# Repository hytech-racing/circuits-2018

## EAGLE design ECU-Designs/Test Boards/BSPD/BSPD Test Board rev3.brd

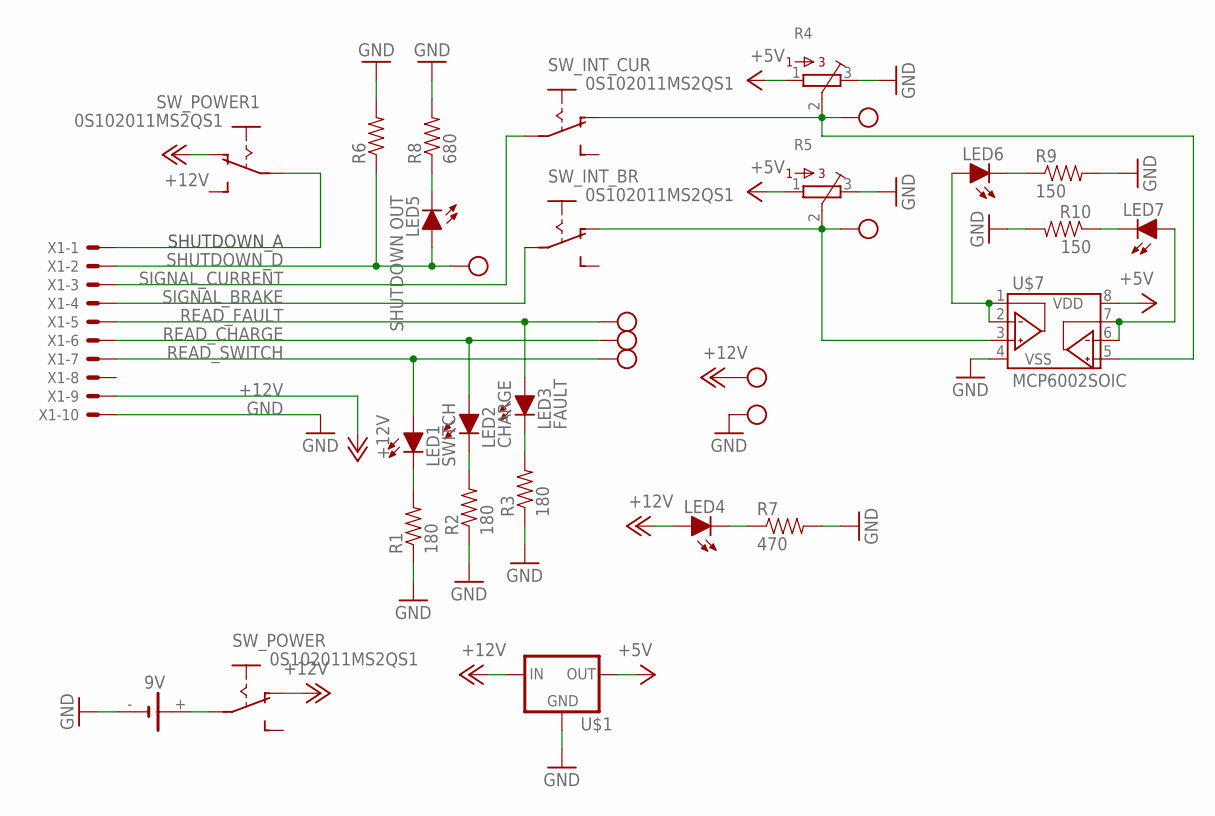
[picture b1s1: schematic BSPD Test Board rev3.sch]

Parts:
9V: 1291-79
LED1: SWITCH; LED-5MM
LED2: CHARGE; LED-5MM
LED3: FAULT; LED-5MM
LED4, LED6, LED7: LED-0805; LED-805
LED5: SHUTDOWN OUT; LED-5MM
R1, R2, R3: 180; 0805
R4, R5: TRIMPOT_3296C; TRIMPOT_3296
R6: RESISTORPTH-1/2W; AXIAL-0.5
R7: 470; 0805
R8: 680; 0805
R9, R10: 150; 0805
SW_INT_BR: 0S102011MS2QS1
SW_INT_CUR: 0S102011MS2QS1
SW_POWER, SW_POWER1: 0S102011MS2QS1
U$1: 5VREG_LM340-NLM340MPX-5.0/NOPB; SOT223
U$2, U$3, U$4, U$5, U$6, U$8, U$9, U$10: TEST_POINT
U$7: MCP6002SOIC; SOIC-08
X1: CONNECTOR-10; MINIFIT_5566-10

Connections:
+5V: R4.1, R5.1, U$1.3 (OUT), U$7.8 (VDD)
+12V: LED4.A, SW_POWER.P$1 (O), SW_POWER1.P$1 (O), U$1.1 (IN), U$5.P$1, X1.9
GND: 9V.-, R1.1, R2.1, R3.1, R4.3, R5.3, R6.P$2 (2), R7.2, R8.2, R9.2, R10.2, U$1.2 (GND), U$1.4 (GND), U$6.P$1, U$7.4 (VSS), X1.10
unnamed: LED1.K (C), R1.2
unnamed: LED2.K (C), R2.2
unnamed: LED3.K (C), R3.2
unnamed: R4.2, SW_INT_CUR.P$1 (O), U$2.P$1, U$7.5 (VINB+)
unnamed: R5.2, SW_INT_BR.P$1 (O), U$3.P$1, U$7.3 (VINA+)
unnamed: 9V.+, SW_POWER.P$2
unnamed: LED4.C, R7.1
unnamed: LED6.A, U$7.1 (VOUTA), U$7.2 (VINA-)
unnamed: LED7.A, U$7.6 (VINB-), U$7.7 (VOUTB)
unnamed: LED6.C, R9.1
unnamed: LED5.K (C), R8.1
unnamed: LED7.C, R10.1
unnamed: SW_POWER1.P$2, X1.1
READ_CHARGE: LED2.A, U$9.P$1, X1.6
READ_FAULT: LED3.A, U$8.P$1, X1.5
READ_SWITCH: LED1.A, U$10.P$1, X1.7
SHUTDOWN_D: LED5.A, R6.P$1 (1), U$4.P$1, X1.2
SIGNAL_BRAKE: SW_INT_BR.P$2, X1.4
SIGNAL_CURRENT: SW_INT_CUR.P$2, X1.3

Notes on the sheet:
SHUTDOWN_A

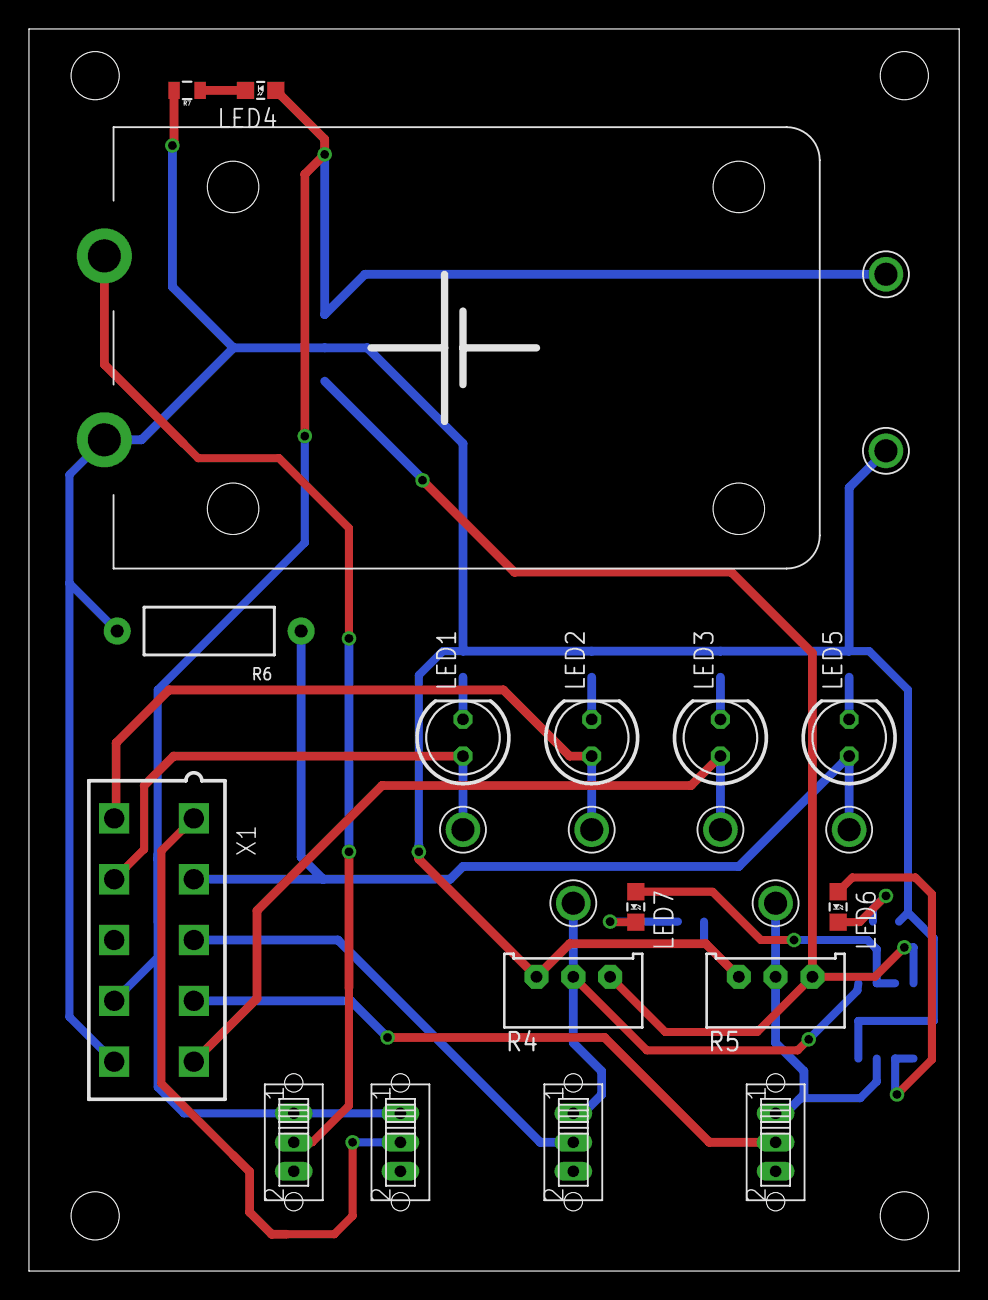
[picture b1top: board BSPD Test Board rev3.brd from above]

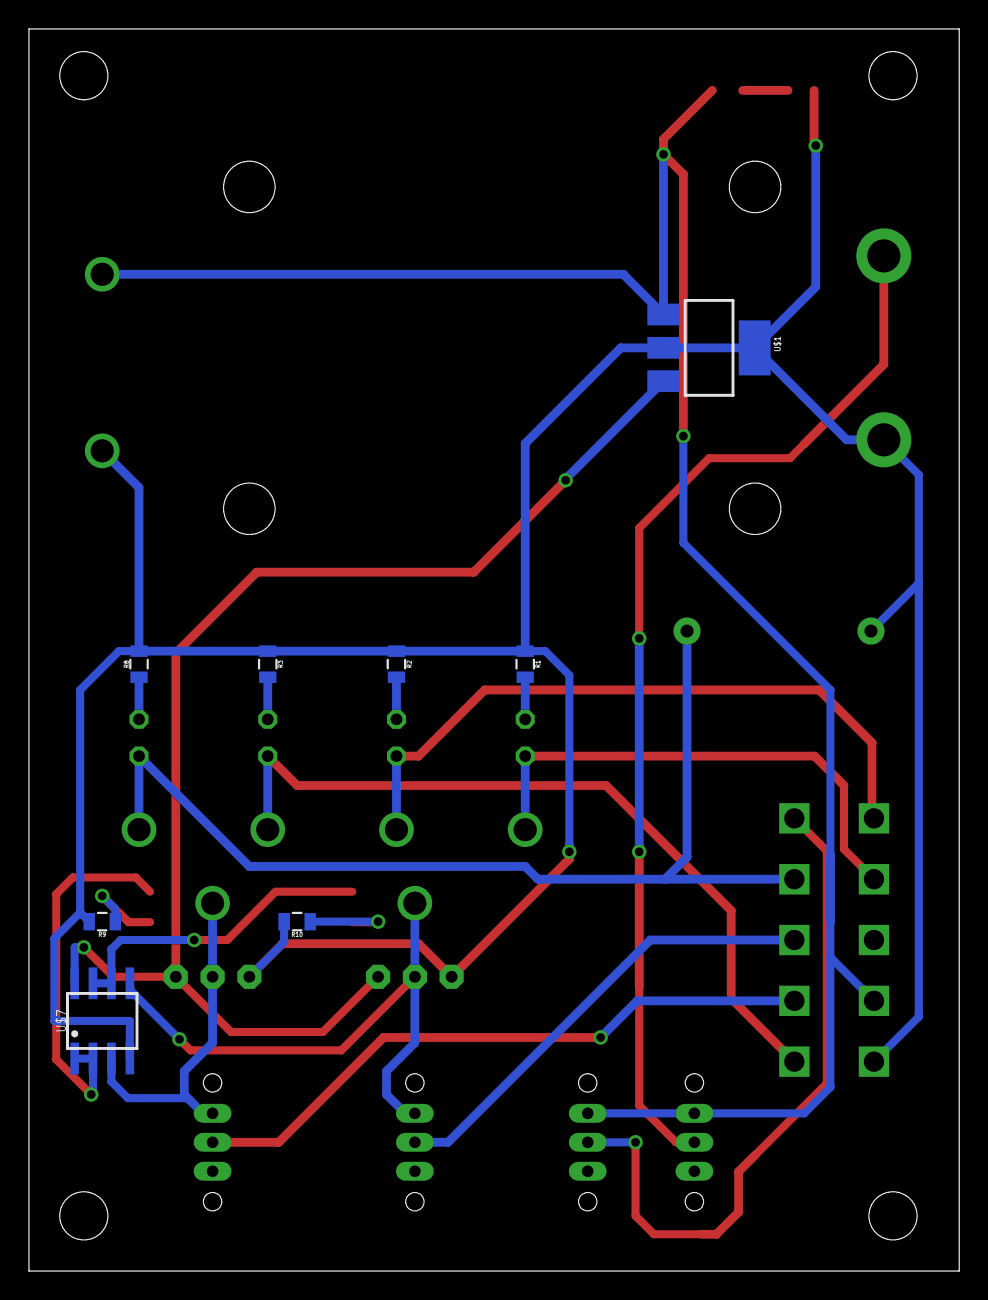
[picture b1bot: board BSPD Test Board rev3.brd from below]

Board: 2 copper layers, 64.2 x 85.8 mm, 33 parts (8 on the bottom side), 22 nets.

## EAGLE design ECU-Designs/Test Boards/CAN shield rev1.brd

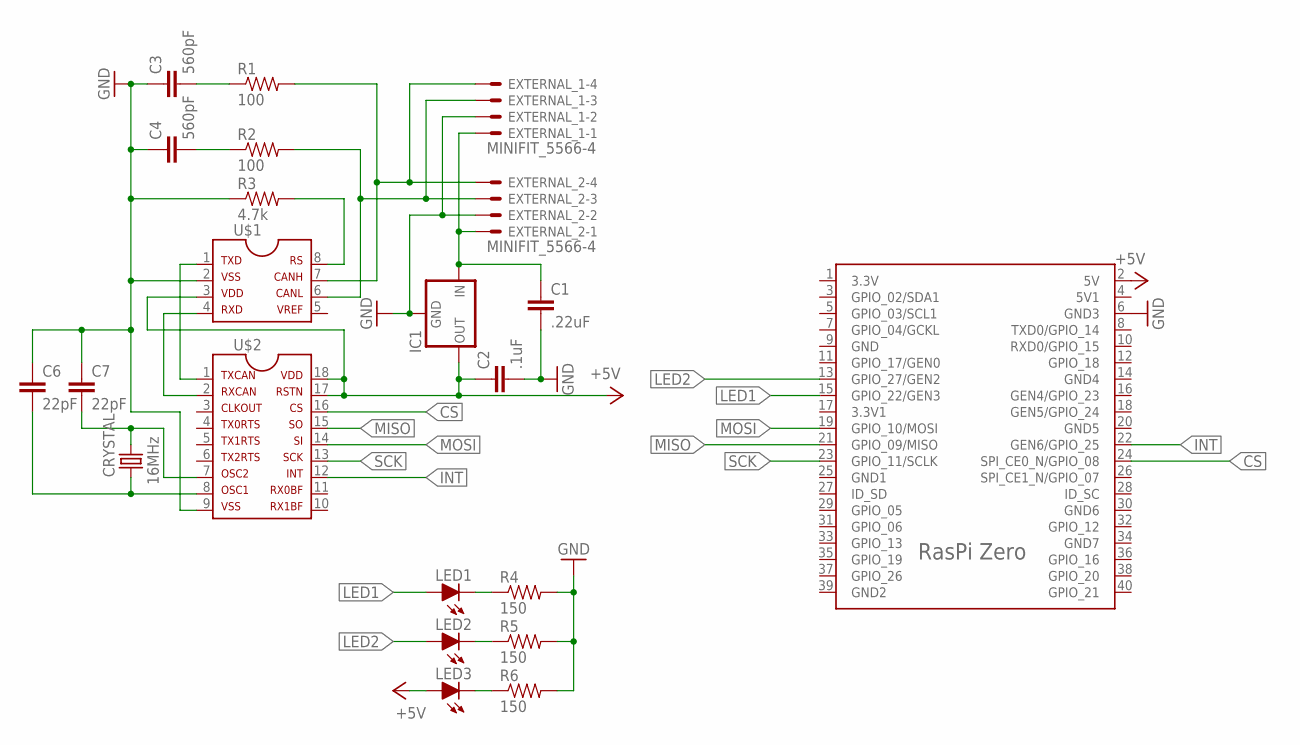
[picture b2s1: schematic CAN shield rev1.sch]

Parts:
C1: .22uF; 0805
C2: .1uF; 0805
C3, C4: 560pF; 0805
C6, C7: 22pF; 0805
CRYSTAL: 16MHz; HC49UP
EXTERNAL_1, EXTERNAL_2: MINIFIT_5566-4
IC1: 5VREG_L7805_HOR; TO-220-H
LED1, LED2, LED3: LED-0805; LED-805
R1, R2: 100; 0805
R3: 4.7k; 0805
R4, R5, R6: 150; 0805
U$1: MCP2551; SOIC-08
U$2: MCP2515SMD; SOIC-18W
U$3: RASPBERRY_PI_ZERO-V1.2

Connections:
+5V: C2.1, IC1.3 (OUT), LED3.A, U$1.3, U$2.17, U$2.18, U$3.2 (5V)
CAN-H: EXTERNAL_1.4, EXTERNAL_2.4, R1.2, U$1.7
CAN-L: EXTERNAL_1.3, EXTERNAL_2.3, R2.2, U$1.6
CS: U$2.16, U$3.24 (SPI_CE0_N/GPIO_08)
GND: C1.2, C2.2, C3.1, C4.1, C6.1, C7.1, EXTERNAL_1.2, EXTERNAL_2.2, IC1.2 (GND), R3.1, R4.2, R5.2, R6.2, U$1.2, U$2.9, U$3.6 (GND3)
INT: U$2.12, U$3.22 (GEN6/GPIO_25)
LED1: LED1.A, U$3.15 (GPIO_22/GEN3)
LED2: LED2.A, U$3.13 (GPIO_27/GEN2)
MISO: U$2.15, U$3.21 (GPIO_09/MISO)
MOSI: U$2.14, U$3.19 (GPIO_10/MOSI)
unnamed: LED1.C, R4.1
unnamed: LED2.C, R5.1
unnamed: C1.1, EXTERNAL_1.1, EXTERNAL_2.1, IC1.1 (IN)
unnamed: LED3.C, R6.1
unnamed: C6.2, CRYSTAL.2, U$2.8
unnamed: U$1.1, U$2.1
unnamed: U$1.4, U$2.2
unnamed: C3.2, R1.1
unnamed: C7.2, CRYSTAL.1, U$2.7
unnamed: R3.2, U$1.8
unnamed: C4.2, R2.1
SCK: U$2.13, U$3.23 (GPIO_11/SCLK)

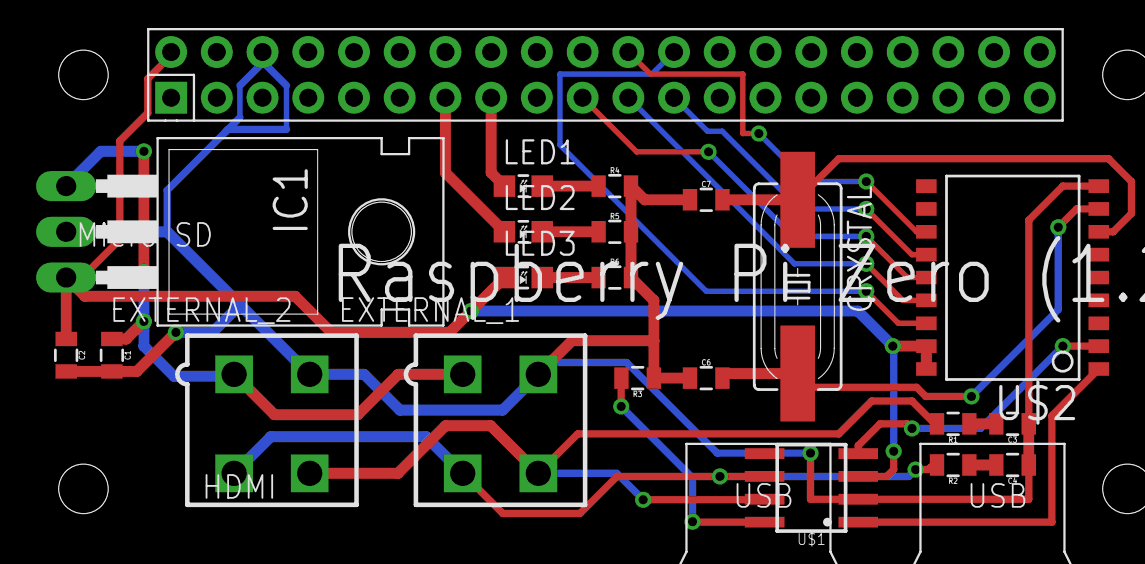
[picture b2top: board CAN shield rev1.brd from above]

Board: 2 copper layers, 22 parts (0 on the bottom side), 22 nets.

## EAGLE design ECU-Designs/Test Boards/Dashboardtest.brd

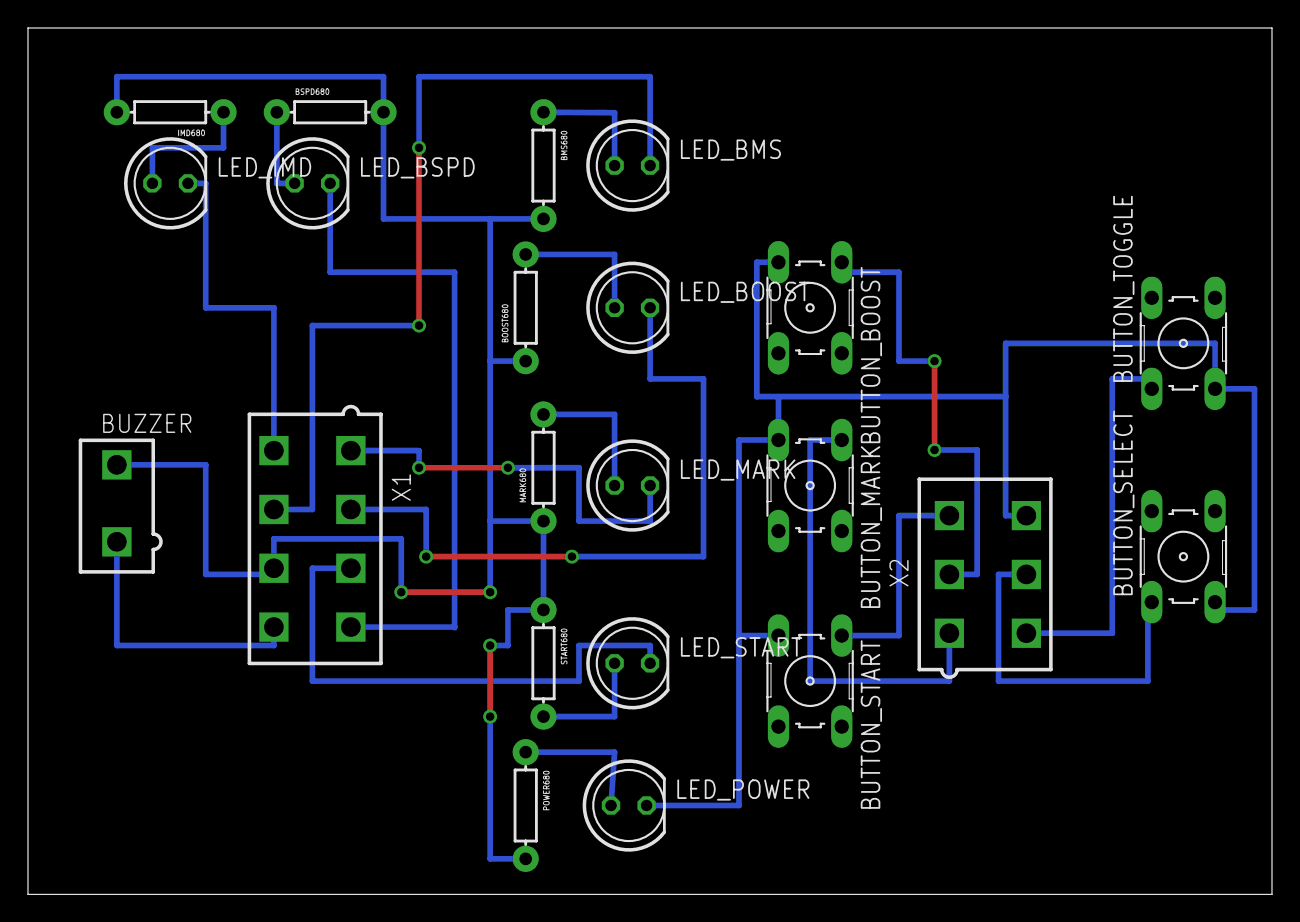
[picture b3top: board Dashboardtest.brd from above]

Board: 2 copper layers, 88.9 x 61.9 mm, 22 parts (0 on the bottom side), 21 nets.

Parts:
BMS680: AXIAL-0.3EZ
BOOST680: AXIAL-0.3EZ
BSPD680: AXIAL-0.3EZ
BUTTON_BOOST: B3F-10XX
BUTTON_MARK: B3F-10XX
BUTTON_SELECT: B3F-10XX
BUTTON_START: B3F-10XX
BUTTON_TOGGLE: B3F-10XX
BUZZER: MINIFIT_5566-2
IMD680: AXIAL-0.3EZ
LED_BMS: LED-5MM
LED_BOOST: LED-5MM
LED_BSPD: LED-5MM
LED_IMD: LED-5MM
LED_MARK: LED-5MM
LED_POWER: LED-5MM
LED_START: LED-5MM
MARK680: AXIAL-0.3EZ
POWER680: AXIAL-0.3EZ
START680: AXIAL-0.3EZ
X1: MINIFIT_5566-8
X2: MINIFIT_5566-6

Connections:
20: BMS680.P$2, BOOST680.P$1, BSPD680.P$2, BUZZER.2, IMD680.P$2, MARK680.P$1, POWER680.P$2, START680.P$1, X1.7
GND: BUTTON_BOOST.3, BUTTON_MARK.3, BUTTON_SELECT.3, BUTTON_START.3, BUTTON_TOGGLE.3, LED_POWER.K, X2.6
LED_IMD: IMD680.P$1, LED_IMD.A
unnamed: LED_POWER.A, POWER680.P$1
unnamed: BMS680.P$1, LED_BMS.A
unnamed: LED_MARK.K, X1.1
unnamed: BSPD680.P$1, LED_BSPD.A
unnamed: LED_BOOST.K, X1.2
unnamed: LED_START.K, X1.3
unnamed: LED_BSPD.K, X1.4
unnamed: BUZZER.1, X1.8
unnamed: LED_IMD.K, X1.5
unnamed: LED_MARK.A, MARK680.P$2
unnamed: BOOST680.P$2, LED_BOOST.A
unnamed: LED_START.A, START680.P$2
unnamed: LED_BMS.K, X1.6
unnamed: BUTTON_MARK.1, X2.1
unnamed: BUTTON_BOOST.1, X2.2
unnamed: BUTTON_START.1, X2.3
unnamed: BUTTON_TOGGLE.1, X2.4
unnamed: BUTTON_SELECT.1, X2.5

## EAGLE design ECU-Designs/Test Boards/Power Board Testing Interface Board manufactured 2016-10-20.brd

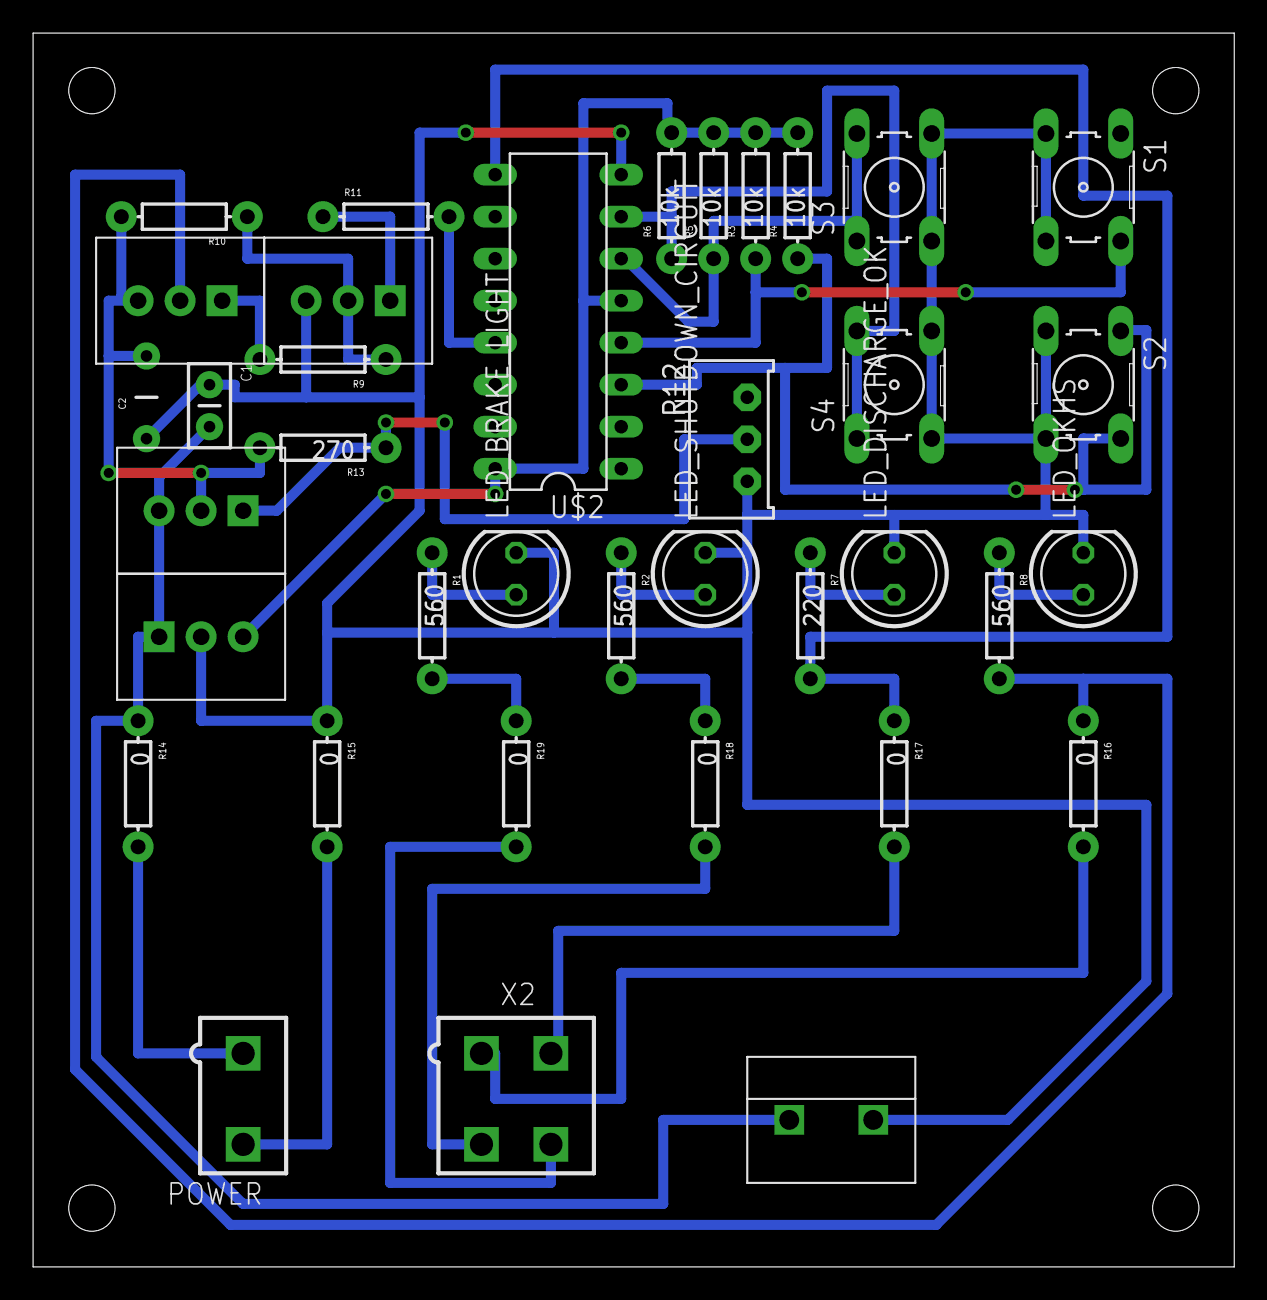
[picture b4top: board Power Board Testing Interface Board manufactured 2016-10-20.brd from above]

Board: 2 copper layers, 72.6 x 74.6 mm, 37 parts (0 on the bottom side), 27 nets.

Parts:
5VSUPPLY: TO-220
C1: .1u; CAP-PTH-SMALLEZ
C2: 2.2u; CAP-PTH-5MM
LED_BRAKE_LIGHT: LED-5MM
LED_DISCHARGE_OK: LED-5MM
LED_OKHS: LED-5MM
LED_SHUTDOWN_CIRCUIT: LED-5MM
NPN: TO-220
OKHS: LM317; TO-220
PNP: TO-220
POWER: MINIFIT_5566-2
R1, R2, R8: 560; AXIAL-0.3EZ
R3, R4, R5, R6: 10k; AXIAL-0.3EZ
R7: 220; AXIAL-0.3EZ
R9, R10, R11: AXIAL-0.3EZ
R12: 1674; TRIMPOT_3296
R13: 270; AXIAL-0.3EZ
R14, R15, R16, R17, R18, R19: 0; AXIAL-0.3EZ
S1, S2, S3, S4: B3F-10XX
U$1: TERMINAL_BLOCK_DG301-02P; DG301-02P
U$2: CD4044B; DIL16
X2: MINIFIT_5566-4

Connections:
5VSUPPLY: 5VSUPPLY.3, R3.P$2, R4.P$2, R5.P$2, R6.P$2, U$2.5, U$2.16
12VSUPPLY: 5VSUPPLY.1, C1.2, OKHS.3, R14.P$1, U$1.1
GND: 5VSUPPLY.2, C1.1, C2.1, LED_BRAKE_LIGHT.K, LED_DISCHARGE_OK.K, LED_OKHS.K, LED_SHUTDOWN_CIRCUIT.K, NPN.3, R12.1, R15.P$1, S1.3, S1.4, S2.3, S2.4, S3.3, S3.4, S4.3, S4.4, U$1.2, U$2.8
unnamed: R1.P$2, R19.P$1
unnamed: LED_BRAKE_LIGHT.A, R1.P$1
unnamed: R2.P$2, R18.P$1
unnamed: LED_SHUTDOWN_CIRCUIT.A, R2.P$1
unnamed: PNP.1, R9.P$2
unnamed: R11.P$2, U$2.13
unnamed: R7.P$2, R17.P$1, U$2.9
unnamed: R3.P$1, S1.2, U$2.4
unnamed: R4.P$1, S2.1, S2.2, U$2.3
unnamed: LED_DISCHARGE_OK.A, R7.P$1
unnamed: LED_OKHS.A, R8.P$1
unnamed: R5.P$1, S3.1, S3.2, U$2.6
unnamed: R6.P$1, S4.1, S4.2, U$2.7
unnamed: PNP.2, R8.P$2, R16.P$1
unnamed: NPN.2, R9.P$1, R10.P$1
unnamed: NPN.1, R11.P$1
unnamed: POWER.2, R15.P$2
unnamed: OKHS.1, R12.2, R13.P$1
unnamed: C2.2, OKHS.2, PNP.3, R10.P$2, R13.P$2
unnamed: POWER.1, R14.P$2
unnamed: R16.P$2, X2.1
unnamed: R17.P$2, X2.2
unnamed: R18.P$2, X2.3
unnamed: R19.P$2, X2.4

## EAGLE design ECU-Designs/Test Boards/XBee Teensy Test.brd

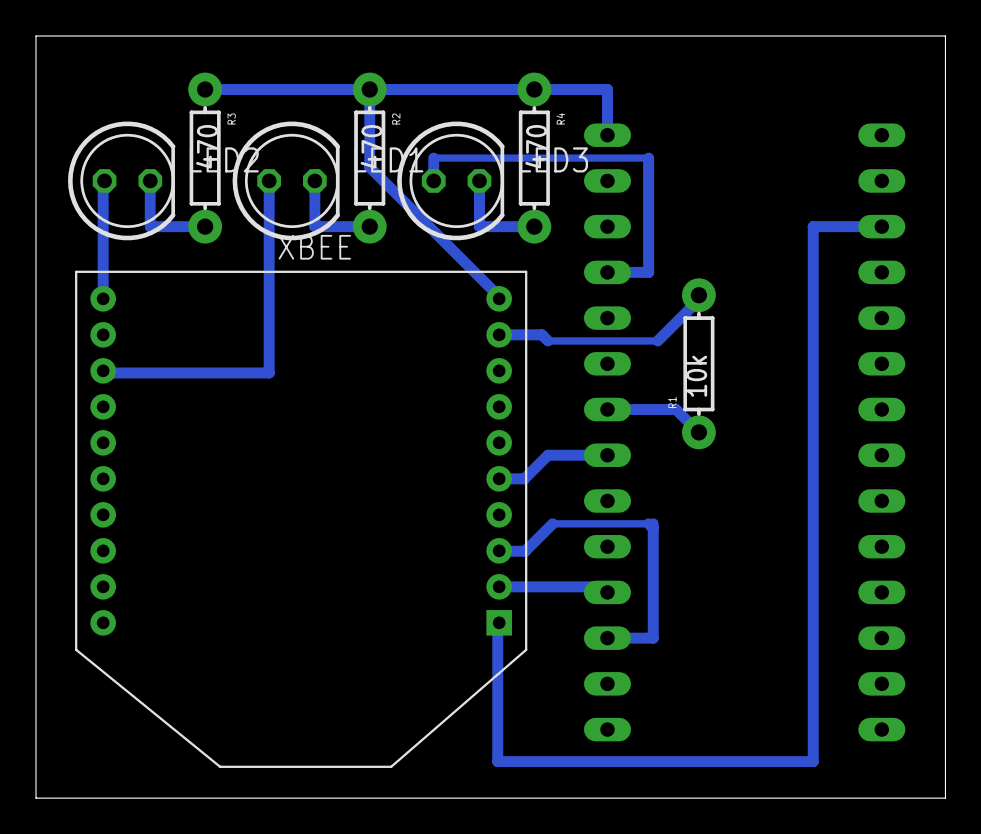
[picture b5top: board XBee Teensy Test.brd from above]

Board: 2 copper layers, 50.5 x 42.3 mm, 9 parts (0 on the bottom side), 13 nets.

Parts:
LED1, LED2, LED3: LED-5MM
R1: 10k; AXIAL-0.3EZ
R2, R3, R4: 470; AXIAL-0.3EZ
U$2: TEENSY_3.2_SIMPLE
XBEE: XBEE

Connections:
GND: R2.P$1, R3.P$1, R4.P$1, U$2.GND, XBEE.10
unnamed: R1.P$2, XBEE.9
unnamed: U$2.D9(RX2), XBEE.2
unnamed: U$2.D10(TX2), XBEE.3
unnamed: U$2.D6, XBEE.5
unnamed: R1.P$1, U$2.D5
unnamed: LED2.A, XBEE.11
unnamed: LED1.A, XBEE.13
unnamed: LED1.K, R2.P$2
unnamed: LED2.K, R3.P$2
unnamed: LED3.K, R4.P$2
unnamed: LED3.A, U$2.D2
VCC: U$2.3.3V, XBEE.1

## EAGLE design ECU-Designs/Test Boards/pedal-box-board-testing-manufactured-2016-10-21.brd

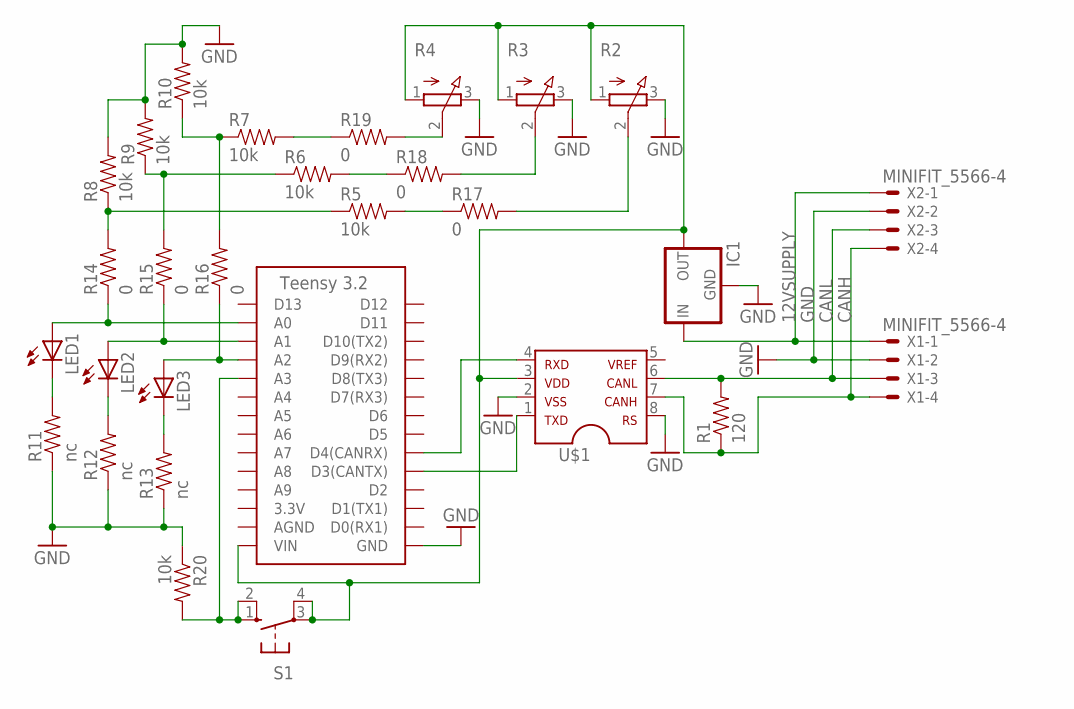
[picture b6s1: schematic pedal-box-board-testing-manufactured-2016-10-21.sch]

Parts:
IC1: 5V_REGULATOR_L7805SWITCHING; TO-220
LED1, LED2, LED3: LED-5MM
R1: 120; AXIAL-0.3
R2, R3, R4: 3RP/1610N
R5, R6, R7, R8, R9, R10, R20: 10k; AXIAL-0.3EZ
R11, R12, R13: nc; AXIAL-0.3EZ
R14, R15, R16, R17, R18, R19: 0; AXIAL-0.3EZ
S1: BTN_10-XX; B3F-10XX
U$1: MCP2551; SOIC-08
U$2: TEENSY_3.2_SIMPLE
X1, X2: MINIFIT_5566-4

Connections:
12VSUPPLY: IC1.1 (IN), X1.1, X2.1
CANH: R1.P$1 (1), U$1.7, X1.4, X2.4
CANL: R1.P$2 (2), U$1.6, X1.3, X2.3
GND: IC1.2 (GND), R2.3 (E), R3.3 (E), R4.3 (E), R8.P$2 (2), R9.P$2 (2), R10.P$2 (2), R11.P$1 (1), R12.P$1 (1), R13.P$1 (1), R20.P$1 (1), U$1.2, U$1.8, U$2.GND, X1.2, X2.2
unnamed: R3.2 (S), R18.P$2 (2)
unnamed: IC1.3 (OUT), R2.1 (A), R3.1 (A), R4.1 (A), S1.3, S1.4 (P1), U$1.3, U$2.VIN
unnamed: LED3.A, R16.P$1 (1), U$2.A2
unnamed: LED2.A, R15.P$1 (1), U$2.A1
unnamed: U$1.1, U$2.D3(CANTX)
unnamed: U$1.4, U$2.D4(CANRX)
unnamed: R5.P$1 (1), R8.P$1 (1), R14.P$2 (2)
unnamed: R2.2 (S), R17.P$2 (2)
unnamed: R4.2 (S), R19.P$2 (2)
unnamed: R7.P$1 (1), R10.P$1 (1), R16.P$2 (2)
unnamed: LED1.K (C), R11.P$2 (2)
unnamed: LED2.K (C), R12.P$2 (2)
unnamed: LED3.K (C), R13.P$2 (2)
unnamed: LED1.A, R14.P$1 (1), U$2.A0
unnamed: R6.P$1 (1), R9.P$1 (1), R15.P$2 (2)
unnamed: R5.P$2 (2), R17.P$1 (1)
unnamed: R7.P$2 (2), R19.P$1 (1)
unnamed: R6.P$2 (2), R18.P$1 (1)
unnamed: R20.P$2 (2), S1.1 (S), S1.2 (S1), U$2.A3

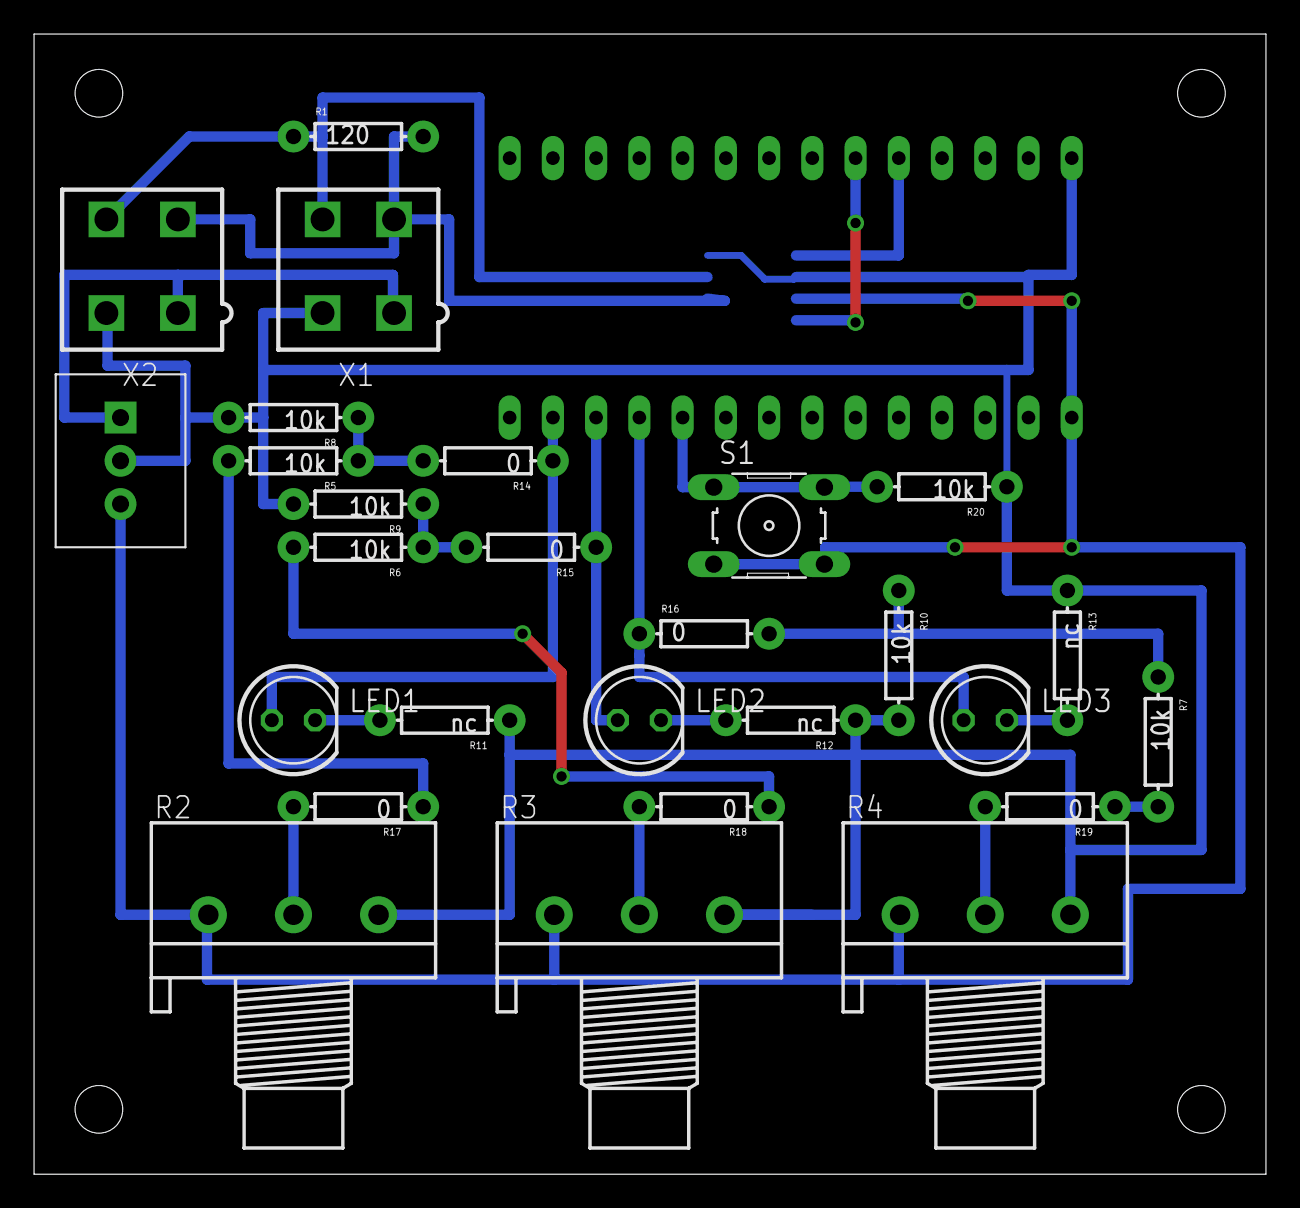
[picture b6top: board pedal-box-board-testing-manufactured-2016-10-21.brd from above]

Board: 2 copper layers, 72.4 x 67.0 mm, 29 parts (1 on the bottom side), 23 nets.

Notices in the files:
parts and their libraries:
SparkFun-FreqCtrl: Licensing: Creative Commons ShareAlike 4.0 International - https://creativecommons.org/licenses/by-sa/4.0
